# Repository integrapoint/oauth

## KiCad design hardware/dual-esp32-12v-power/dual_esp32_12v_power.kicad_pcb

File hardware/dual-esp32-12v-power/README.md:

# Dual ESP32-S3-1.69 12V Power Board

A small 2-layer PCB that takes a single 12V DC input and produces two
independently-switched, independently-fused 5V outputs, each sized to run
one ESP32-S3-1.69 round-LCD dev board (the kind shown breadboarded with a
dual-rail buck module in the reference photo for this project).

Board size: 200 x 132 mm, 2-layer (top signal, bottom solid GND pour).

## How it was built

This board was generated entirely from Python code driving KiCad's
`pcbnew` scripting API (`build_board.py`) rather than drawn by hand in the
KiCad GUI - component placement, net assignment, copper routing and the
ground-pour zone are all produced programmatically. `check_board.py` is a
from-scratch geometric verifier (built because this KiCad 7.0 CLI build
has no `pcb drc` subcommand - that landed in KiCad 8) that checks every
net is actually routed and that no two different-net copper features
(traces or pads) violate clearance on the same layer. The final board
passes that check with zero issues. `fill_zone.py` performs the GND zone
fill (KiCad's `ZONE_FILLER` segfaults when run with no display attached,
so this is run once under `xvfb-run`).

**What was not independently verified:** this environment's network
egress blocks every chip-vendor datasheet host (ti.com, diodes.com,
alldatasheet, lcsc, etc.), so the LM2596 pinout/application-circuit and
the PJ-102A jack pin mapping used below are from well-established,
widely-documented reference designs rather than a freshly pulled
datasheet. **Before ordering assembly or populating parts, cross-check
the LM2596 pinout and the ON/OFF pin behavior against your specific
vendor's datasheet.**

## Circuit description

```
12V IN --[TVS]--[PTC fuse]--[reverse-polarity diode]--> V12 (protected 12V rail)
                                                            |
                                        +-------------------+-------------------+
                                        |                                       |
                                  Channel A                               Channel B
                                  (identical)                             (identical)
```

Each channel is an independent **LM2596T-5.0** (TO-220-5, fixed 5V output,
synchronous-ish buck, 3A capable) with the standard minimal application
circuit:

- `CIN` (100uF/25V) on the regulator input
- `L` (33uH) + `D` (1N5822 catch diode) forming the switching node
- `COUT` (220uF/25V) on the regulated 5V output, with the FEEDBACK pin
  wired straight back to it (this is a **fixed**-output part - FEEDBACK
  still has to be tied to VOUT per the standard LM2596 application
  circuit, it just doesn't need a resistor divider)
- An **EN pull-up + slide switch** on the ON/OFF pin: a 10k resistor
  holds ON/OFF high (regulator OFF) by default, and the slide switch
  pulls it to GND to enable the regulator. This means the switch only
  ever carries a couple of mA, not the load current.
- A **500mA-hold PTC fuse** on the regulated output, in series with a
  power-good LED and a 2-pin 2.54mm header (pin 1 = +5V, pin 2 = GND)
  for wiring to the ESP32-S3-1.69 board.

Shared input protection ahead of both channels:

- **TVS diode** (P6KE15A) across the raw input for surge/ESD clamping
- **PTC resettable fuse** (~2A hold) for overall overcurrent/short
  protection
- **Series Schottky diode** (1N5822) for reverse-polarity protection
  (small ~0.3-0.5V drop, irrelevant with 12V in and a switching
  regulator downstream)
- 100nF ceramic + a green power-good LED

## Why two separate regulators instead of one shared 5V rail

Each ESP32-S3 board gets its own regulator, inductor, output cap, fuse
and switch, so the two channels are electrically independent: a short or
brownout on one ESP32 board can't drag down or reset the other, and each
board can be power-cycled independently with its own slide switch.

## IMPORTANT - verify before you power up an ESP32-S3-1.69 board

The two channels output a fixed **5V**, matching a typical 5V/VIN pin
broken out on ESP32 dev boards (this is what the loose wires in the
reference photo appear to be going into). **Do not** wire this into a
LiPo/battery-only JST-PH connector on your specific board - those are
usually a raw ~3.7-4.2V battery input feeding an onboard charge IC, and
5V there can damage the board. Check your exact ESP32-S3-1.69 variant's
silkscreen/schematic for which pin actually wants 5V before connecting.

## Files

- `dual_esp32_12v_power.kicad_pcb` / `.kicad_pro` - the KiCad 7 project
- `build_board.py` - regenerates the `.kicad_pcb` from scratch
- `check_board.py` - the geometric connectivity/clearance verifier
- `fill_zone.py` - fills the bottom-layer GND zone (run under `xvfb-run`)
- `BOM.csv` - full bill of materials with suggested part numbers
- `gerbers/` - Gerber X2, Excellon drill (PTH/NPTH separated), and a
  CSV placement (position) file
- `dual_esp32_12v_power_gerbers.zip` - the `gerbers/` folder pre-zipped,
  ready to drag-and-drop into PCBWay's instant-quote uploader
- `docs/preview_top.png`, `docs/preview_bottom.png` - rendered top
  copper/silkscreen and bottom copper (GND pour) previews

## Ordering from PCBWay

1. Go to PCBWay's instant quote / PCB Prototype page and upload
   `dual_esp32_12v_power_gerbers.zip` directly - PCBWay auto-reads the
   board outline and layer count from the Gerber set.
2. Suggested options: 2 layers, 1.6mm thickness, 1oz copper, any solder
   mask/silkscreen color, HASL (lead-free) or ENIG finish - all default
   PCBWay options work fine for this design (no fine-pitch/impedance
   requirements).
3. If you want PCBWay to also assemble it (PCBA), upload `BOM.csv` and
   `gerbers/dual_esp32_12v_power-all-pos.csv` (placement file) - you'll
   likely need to fill in / confirm exact distributor part numbers for
   the electrolytic caps, inductor and switch since those were specified
   generically here.
4. Otherwise, hand-solder it yourself - every part on this board is
   through-hole by design.

## Regenerating the board

```
python3 build_board.py          # rebuild dual_esp32_12v_power.kicad_pcb from scratch
python3 check_board.py          # verify: 0 issues expected
xvfb-run -a python3 fill_zone.py  # fill the GND zone (needed before Gerber export)
kicad-cli pcb export gerbers -o gerbers/ dual_esp32_12v_power.kicad_pcb
kicad-cli pcb export drill -o gerbers/ --format excellon --drill-origin absolute --excellon-separate-th dual_esp32_12v_power.kicad_pcb
kicad-cli pcb export pos -o gerbers/dual_esp32_12v_power-all-pos.csv --format csv --units mm --side both dual_esp32_12v_power.kicad_pcb
```

Requires `kicad` (>=7.0, for `pcbnew`/`kicad-cli`) and `xvfb` installed.

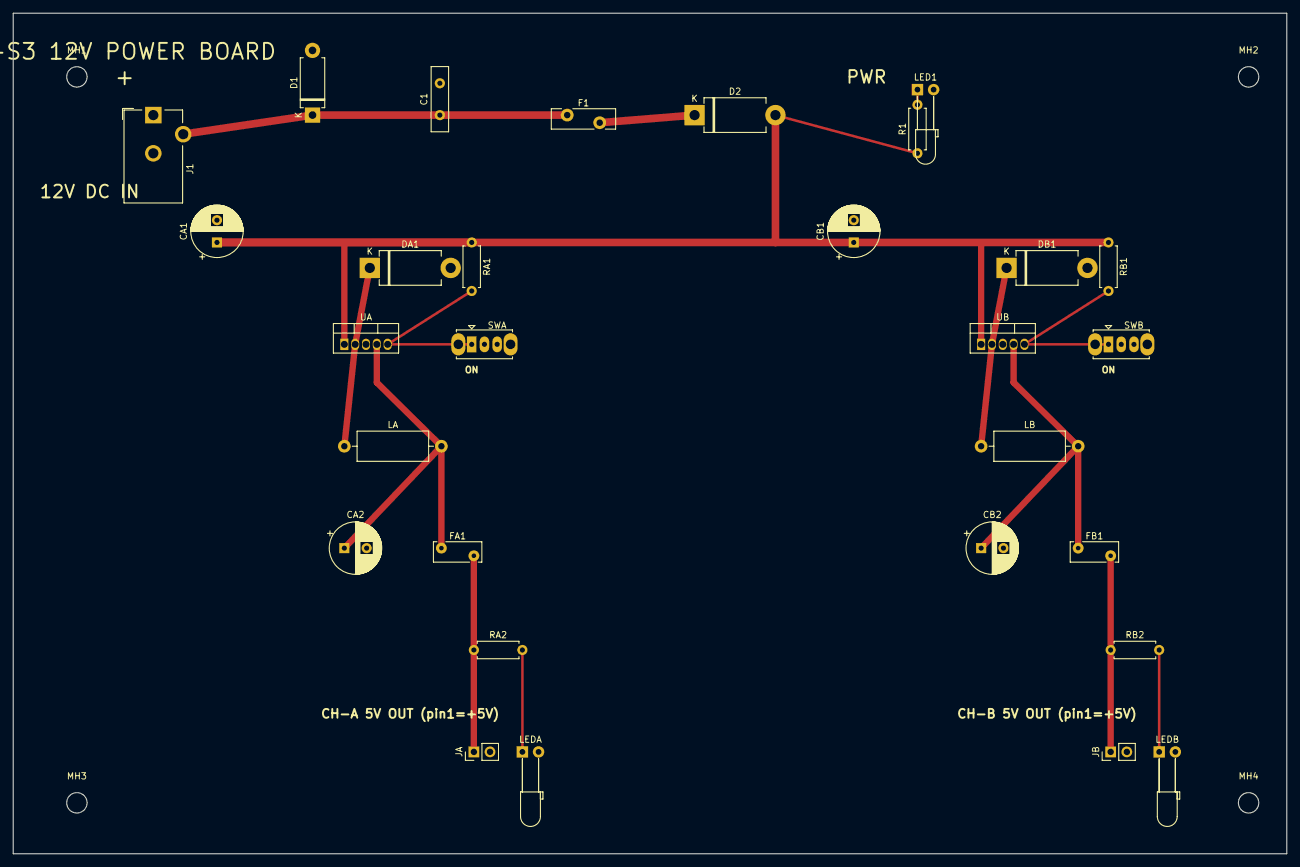
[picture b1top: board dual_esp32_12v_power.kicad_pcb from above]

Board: 2 copper layers, 200.0 x 132.0 mm, 33 parts (0 on the bottom side), 15 nets.

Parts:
C1: C_Disc_D10.0mm_W2.5mm_P5.00mm
CA1, CA2: CP_Radial_D8.0mm_P3.50mm
CB1, CB2: CP_Radial_D8.0mm_P3.50mm
D1: D_DO-15_P10.16mm_Horizontal
D2: D_DO-201AD_P12.70mm_Horizontal
DA1: D_DO-201AD_P12.70mm_Horizontal
DB1: D_DO-201AD_P12.70mm_Horizontal
F1: Fuse_Bourns_MF-RG400
FA1: Fuse_Bourns_MF-RHT050
FB1: Fuse_Bourns_MF-RHT050
J1: BarrelJack_CUI_PJ-102AH_Horizontal
JA: PinHeader_1x02_P2.54mm_Vertical
JB: PinHeader_1x02_P2.54mm_Vertical
LA: L_Axial_L11.0mm_D4.5mm_P15.24mm_Horizontal_Fastro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; L_Axial_L11.0mm_D4.5mm_P15.24mm_Horizontal_Fastron_MECC
LB: L_Axial_L11.0mm_D4.5mm_P15.24mm_Horizontal_Fastro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; L_Axial_L11.0mm_D4.5mm_P15.24mm_Horizontal_Fastron_MECC
LED1: LED_D3.0mm_Horizontal_O6.35mm_Z2.0mm
LEDA: LED_D3.0mm_Horizontal_O6.35mm_Z2.0mm
LEDB: LED_D3.0mm_Horizontal_O6.35mm_Z2.0mm
MH1, MH2, MH3, MH4: MountingHole_3.2mm_M3
R1: R_Axial_DIN0207_L6.3mm_D2.5mm_P7.62mm_Horizontal
RA1, RA2: R_Axial_DIN0207_L6.3mm_D2.5mm_P7.62mm_Horizontal
RB1, RB2: R_Axial_DIN0207_L6.3mm_D2.5mm_P7.62mm_Horizontal
SWA: SW_Slide_SPDT_Straight_CK_OS102011MS2Q
SWB: SW_Slide_SPDT_Straight_CK_OS102011MS2Q
UA: TO-220-5_Vertical
UB: TO-220-5_Vertical

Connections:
EN_A: RA1.2, SWA.1, UA.5
EN_B: RB1.2, SWB.1, UB.5
GND: C1.2, CA1.2, CA2.2, CB1.2, CB2.2, D1.2, DA1.2, DB1.2, J1.1, JA.2, JB.2, LED1.2, LEDA.2, LEDB.2, SWA.2, SWB.2, UA.3, UB.3
LEDA_MID: LEDA.1, RA2.2
LEDB_MID: LEDB.1, RB2.2
PWRLED_MID: LED1.1, R1.2
SWA_5V: DA1.1, LA.1, UA.2
SWB_5V: DB1.1, LB.1, UB.2
V5A_OUT: FA1.2, JA.1, RA2.1
V5A_PRE: CA2.1, FA1.1, LA.2, UA.4
V5B_OUT: FB1.2, JB.1, RB2.1
V5B_PRE: CB2.1, FB1.1, LB.2, UB.4
V12: CA1.1, CB1.1, D2.2, R1.1, RA1.1, RB1.1, UA.1, UB.1
VIN_FUSED: D2.1, F1.2
VIN_RAW: C1.1, D1.1, F1.1, J1.3
